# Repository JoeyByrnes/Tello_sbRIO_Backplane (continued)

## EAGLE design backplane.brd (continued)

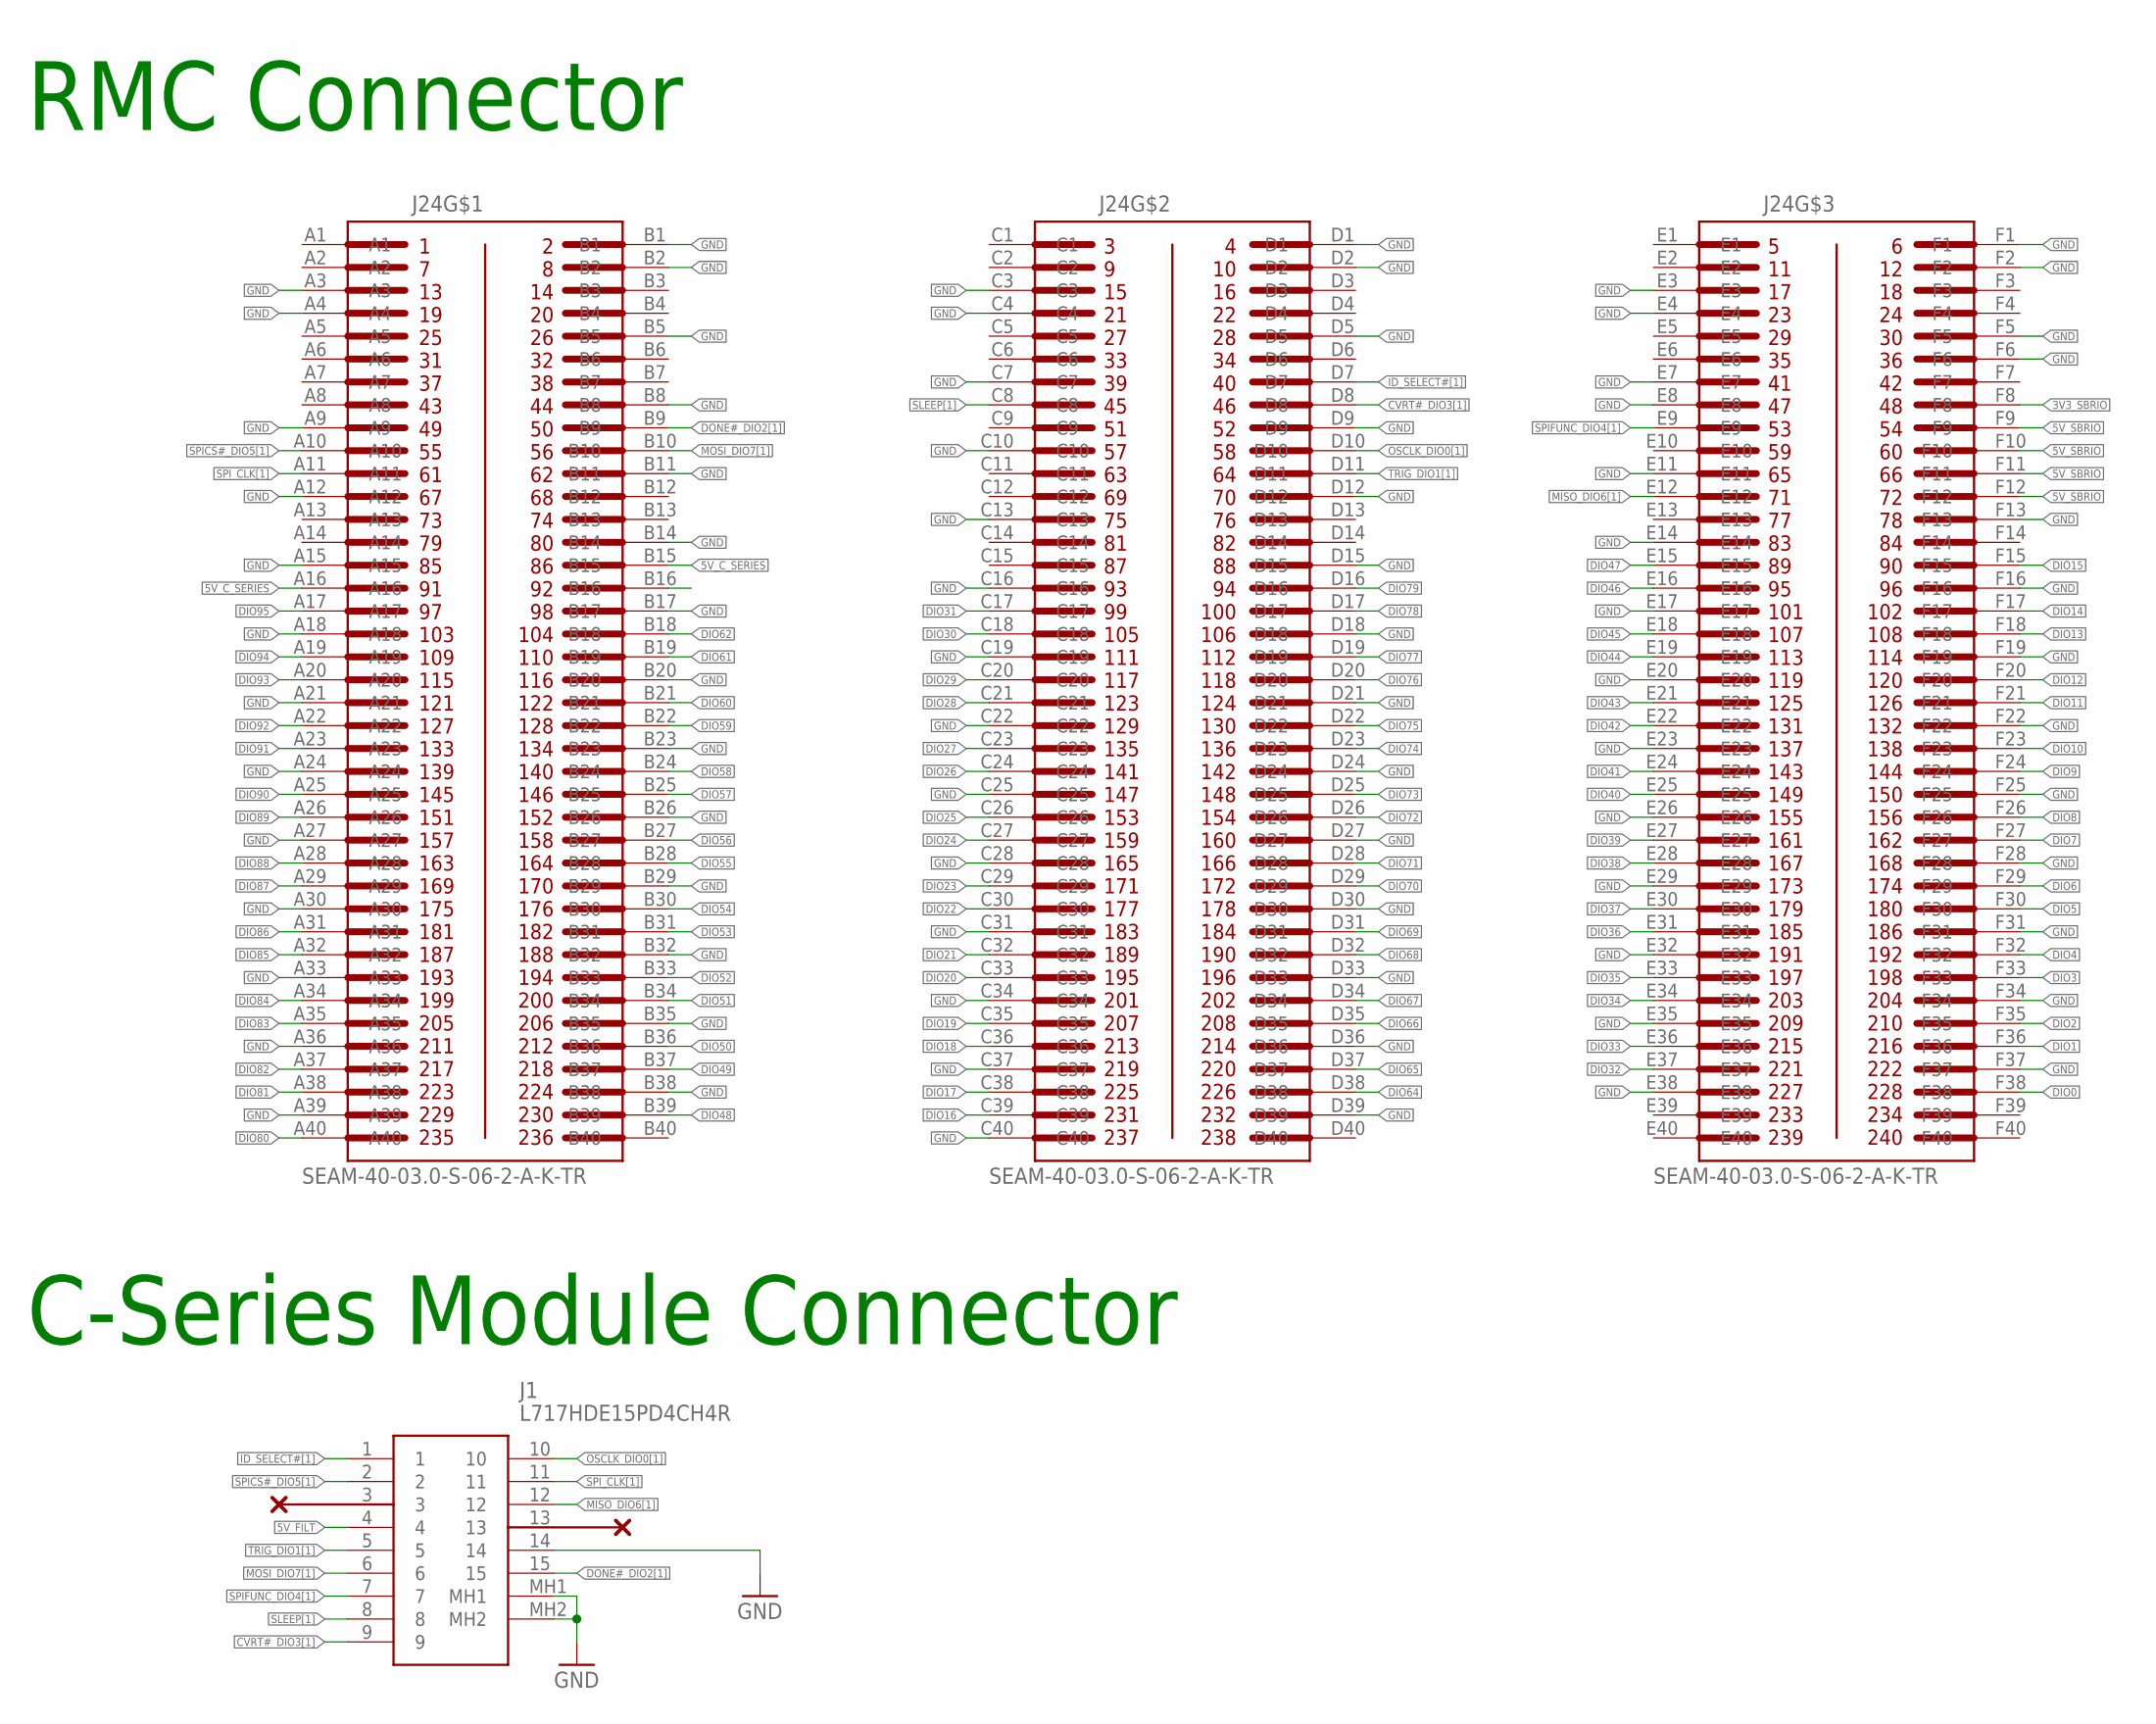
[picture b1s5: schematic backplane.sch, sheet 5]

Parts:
J1: L717HDE15PD4CH4R
J24: SEAM-40-03.0-S-06-2-A-K-TR; SAMTEC_SEAM-40-03.0-S-06-2-A-K-TR

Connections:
3V3_SBRIO: J24.F8; also elsewhere on the board
5V_C_SERIES: J24.A16, J24.B15; also elsewhere on the board
5V_FILT: J1.4; also elsewhere on the board
5V_SBRIO: J24.F9, J24.F10, J24.F11, J24.F12; also elsewhere on the board
CVRT#_DIO3[1]: J1.9, J24.D8
DIO0: J24.F38; also elsewhere on the board
DIO1: J24.F36; also elsewhere on the board
DIO2: J24.F35; also elsewhere on the board
DIO3: J24.F33; also elsewhere on the board
DIO4: J24.F32; also elsewhere on the board
DIO5: J24.F30; also elsewhere on the board
DIO6: J24.F29; also elsewhere on the board
DIO7: J24.F27; also elsewhere on the board
DIO8: J24.F26; also elsewhere on the board
DIO9: J24.F24; also elsewhere on the board
DIO10: J24.F23; also elsewhere on the board
DIO11: J24.F21; also elsewhere on the board
DIO12: J24.F20; also elsewhere on the board
DIO13: J24.F18; also elsewhere on the board
DIO14: J24.F17; also elsewhere on the board
DIO15: J24.F15; also elsewhere on the board
DIO16: J24.C39; also elsewhere on the board
DIO17: J24.C38; also elsewhere on the board
DIO18: J24.C36
DIO19: J24.C35
DIO20: J24.C33
DIO21: J24.C32; also elsewhere on the board
DIO22: J24.C30; also elsewhere on the board
DIO23: J24.C29; also elsewhere on the board
DIO24: J24.C27; also elsewhere on the board
DIO25: J24.C26; also elsewhere on the board
DIO26: J24.C24; also elsewhere on the board
DIO27: J24.C23; also elsewhere on the board
DIO28: J24.C21; also elsewhere on the board
DIO29: J24.C20; also elsewhere on the board
DIO30: J24.C18; also elsewhere on the board
DIO31: J24.C17; also elsewhere on the board
DIO32: J24.E37; also elsewhere on the board
DIO33: J24.E36; also elsewhere on the board
DIO34: J24.E34; also elsewhere on the board
DIO35: J24.E33; also elsewhere on the board
DIO36: J24.E31; also elsewhere on the board
DIO37: J24.E30; also elsewhere on the board
DIO38: J24.E28; also elsewhere on the board
DIO39: J24.E27; also elsewhere on the board
DIO40: J24.E25; also elsewhere on the board
DIO41: J24.E24; also elsewhere on the board
DIO42: J24.E22; also elsewhere on the board
DIO43: J24.E21; also elsewhere on the board
DIO44: J24.E19; also elsewhere on the board
DIO45: J24.E18; also elsewhere on the board
DIO46: J24.E16; also elsewhere on the board
DIO47: J24.E15; also elsewhere on the board
DIO48: J24.B39; also elsewhere on the board
DIO49: J24.B37; also elsewhere on the board
DIO50: J24.B36
DIO51: J24.B34
DIO52: J24.B33; also elsewhere on the board
DIO53: J24.B31; also elsewhere on the board
DIO54: J24.B30; also elsewhere on the board
DIO55: J24.B28; also elsewhere on the board
DIO56: J24.B27; also elsewhere on the board
DIO57: J24.B25; also elsewhere on the board
DIO58: J24.B24; also elsewhere on the board
DIO59: J24.B22; also elsewhere on the board
DIO60: J24.B21; also elsewhere on the board
DIO61: J24.B19; also elsewhere on the board
DIO62: J24.B18; also elsewhere on the board
DIO64: J24.D38
DIO65: J24.D37
DIO66: J24.D35
DIO67: J24.D34
DIO68: J24.D32
DIO69: J24.D31
DIO70: J24.D29
DIO71: J24.D28
DIO72: J24.D26
DIO73: J24.D25
DIO74: J24.D23
DIO75: J24.D22
DIO76: J24.D20
DIO77: J24.D19; also elsewhere on the board
DIO78: J24.D17; also elsewhere on the board
DIO79: J24.D16; also elsewhere on the board
DIO80: J24.A40; also elsewhere on the board
DIO81: J24.A38; also elsewhere on the board
DIO82: J24.A37; also elsewhere on the board
DIO83: J24.A35; also elsewhere on the board
DIO84: J24.A34
DIO85: J24.A32; also elsewhere on the board
DIO86: J24.A31; also elsewhere on the board
DIO87: J24.A29; also elsewhere on the board
DIO88: J24.A28; also elsewhere on the board
DIO89: J24.A26; also elsewhere on the board
DIO90: J24.A25; also elsewhere on the board
DIO91: J24.A23; also elsewhere on the board
DIO92: J24.A22; also elsewhere on the board
DIO93: J24.A20; also elsewhere on the board
DIO94: J24.A19; also elsewhere on the board
DIO95: J24.A17; also elsewhere on the board
DONE#_DIO2[1]: J1.15, J24.B9
GND: J1.14, J1.MH1, J1.MH2, J24.A3, J24.A4, J24.A9, J24.A12, J24.A15, J24.A18, J24.A21, J24.A24, J24.A27, J24.A30, J24.A33, J24.A36, J24.A39, J24.B1, J24.B2, J24.B5, J24.B8, J24.B11, J24.B14, J24.B17, J24.B20, J24.B23, J24.B26, J24.B29, J24.B32, J24.B35, J24.B38, J24.C3, J24.C4, J24.C7, J24.C10, J24.C13, J24.C16, J24.C19, J24.C22, J24.C25, J24.C28, J24.C31, J24.C34, J24.C37, J24.C40, J24.D1, J24.D2, J24.D5, J24.D9, J24.D12, J24.D15, J24.D18, J24.D21, J24.D24, J24.D27, J24.D30, J24.D33, J24.D36, J24.D39, J24.E3, J24.E4, J24.E7, J24.E8, J24.E11, J24.E14, J24.E17, J24.E20, J24.E23, J24.E26, J24.E29, J24.E32, J24.E35, J24.E38, J24.F1, J24.F2, J24.F5, J24.F6, J24.F13, J24.F16, J24.F19, J24.F22, J24.F25, J24.F28, J24.F31, J24.F34, J24.F37; also elsewhere on the board
ID_SELECT#[1]: J1.1, J24.D7
MISO_DIO6[1]: J1.12, J24.E12
MOSI_DIO7[1]: J1.6, J24.B10
OSCLK_DIO0[1]: J1.10, J24.D10
SLEEP[1]: J1.8, J24.C8
SPICS#_DIO5[1]: J1.2, J24.A10
SPIFUNC_DIO4[1]: J1.7, J24.E9
SPI_CLK[1]: J1.11, J24.A11
TRIG_DIO1[1]: J1.5, J24.D11

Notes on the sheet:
RMC Connector
C-Series Module Connector

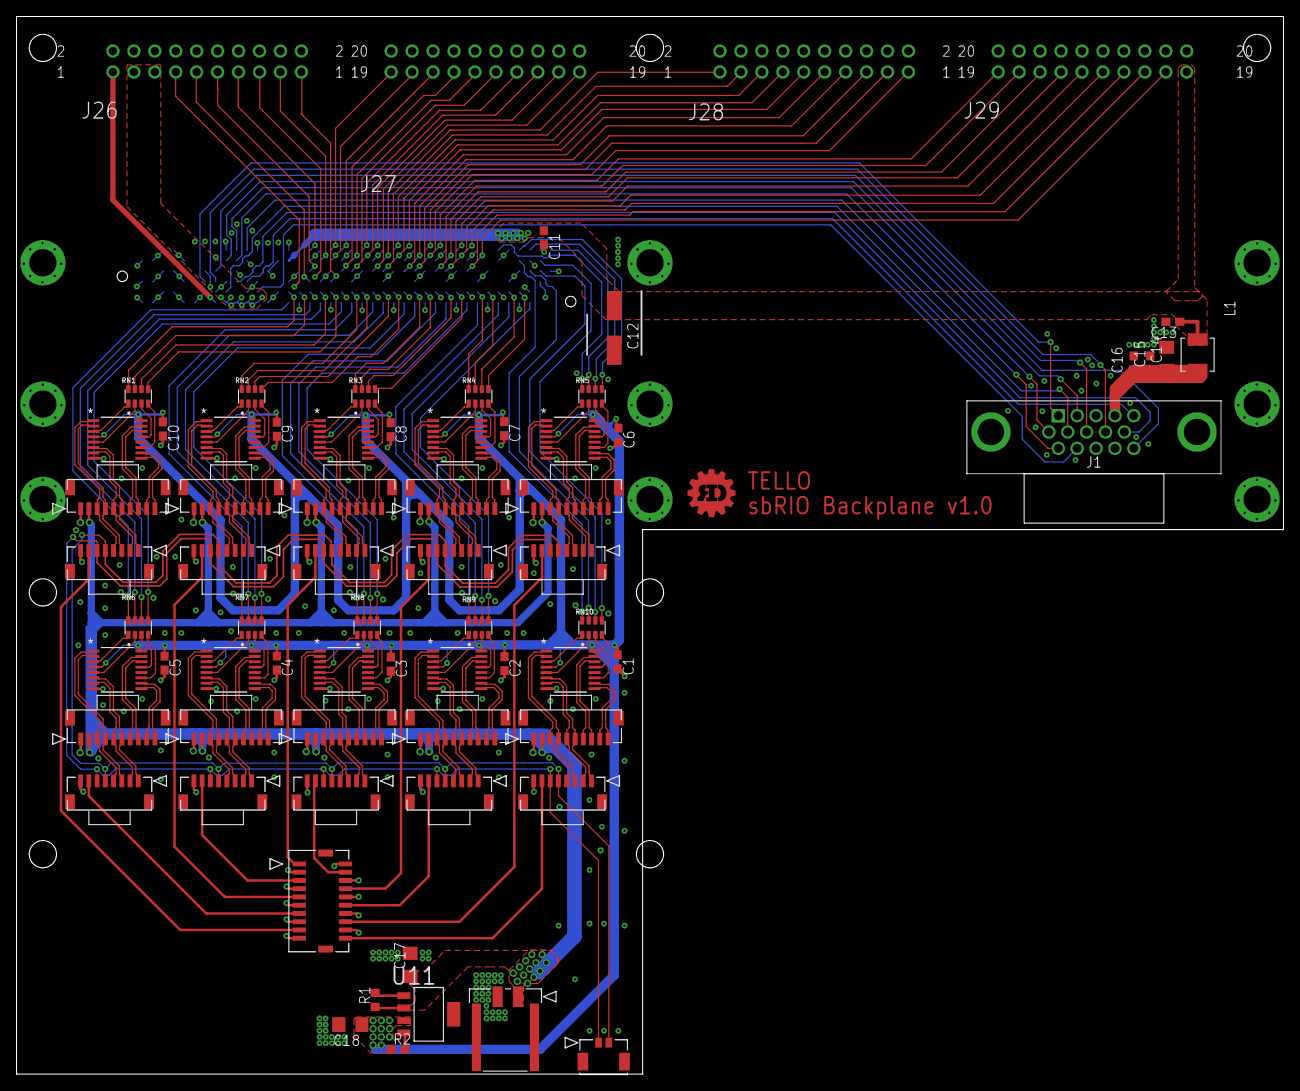
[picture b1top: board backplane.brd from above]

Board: 4 copper layers, 153.7 x 128.3 mm, 71 parts (1 on the bottom side), 229 nets.

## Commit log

2022-07-04 Started layout of pcb
2022-07-08 Started routing Encoder/AMC Connectors
2022-07-10 encoder/amc connectors mostly routed
2022-07-10 adjusted silkscreen
2022-07-11 many RMC connections routed
2022-07-11 Routed power to AMC/encoder connectors and drivers
2022-07-11 added bypass caps and routed G pins on drivers
2022-07-15 added filter, 3v3 reg, and extra DIO
2022-08-15 DRC Checks passed, in-depth review INCOMPLETE
2022-08-16 Design Review Finished, Ready to order
